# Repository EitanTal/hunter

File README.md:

# Intro

This is a recreation of an Old-school Hunter fan remote

## Digital signals

Every packet is as follows:

   [`address`][`opcode`]

address is 5 bits long, opcode is 8 bits long. Address used = 0b01111

### Packets & Opcodes

* light:    0x0F (01111) 0x1 (00000001)
* fan off:  0x0F (01111) 0x2 (00000010)
* fan rev:                   (00000100)
* fan 3:                     (00001000)
* fan 2:                     (00010000)
* fan 1:    0x0F             (00100000)

## Pulse layout

short pulse: (0)

      _
    __

long pulse: (1)

     __
    _

## Pulse timing

length of each character: 328.4us (0.3284ms)

every 1 bit = 8us.
41 bits = one unit.
~16 bytes per triplet.

This equals a baudrate of 3045

The bit burst must repeat 16 times.
There must be exactly 10ms gap between each bit burst.

## Radio notes

### Carrier

The chosen carrier is 302MHz. The original remote is inconsistent on its carrier wave, ranging from 300 to 305.

### Modulation

On-off-keying modulation is used. (AM)

### RF backend

This implementation utilizes TI CC1101 as the RF backend. The original hunter remote presumably used a ferrite core antenna. More details are available in eariler revisions.

As an antenna, a 30cm wire is used.

For power, 0db is currently used

## Breadboard notes

CC1101 operates on 3v3 max. Resistor divider used on Arduino -> CC1101

Relevant pins on the pinheader of the eval board of CC1101:
| Color   | Pin   |  |   Pin  | Color   |
|---------|-------|--|--------|---------|
|  Brown  | VCC   |  | VCC    | Red     |
|  Orange | SCK   |  | MOSI   | Yellow  |
|  Green  | GDO2  |  | MISO   | Blue    |
|  Purple | GDO0  |  | CSN    | Grey    |
|  White  | GND   |  | GND    | Black   |

The pins as they connect to my breadboard:
| Color   | Pin   |  |   Pin  | Color   |
|---------|-------|--|--------|---------|
| (Black) |GND    |  |    VCC |   (Red) |
| (Blue)  |MISO   |  |   MOSI |(Yellow) |
| (Orange)|SCK    |  |    CSN |  (Grey) |
|         |       |  |   GDO0 |(Purple) |

Relevant pins on the arduino:
|Number|Function|Comment                  |
|------|--------|-------------------------|
|10    | SS     | (Active low)            |
|11    | MOSI   |                         |
|12    | MISO   |                         |
|13    | SCLK   |                         |
|2     | GDO0   | (Interrupt line 0, PD2) |

Breadboard jumper cables:
arduino-breadboard line
2-21
7-19
10-15
11-13
12-17
13-9

## STM8 pins

|Arduino|Function|207K (Eval board)   |101F (Target)  |
|-------|--------|--------------------|---------------|
|10     | SS     |PE5 (D10)           |PB4            |
|11     | MOSI   |PC6 (D11)           |PB6            |
|12     | MISO   |PC7 (D12)           |PB7            |
|13     | SCLK   |PC5 (D13)           |PB5            |
|2      | GDO0   |PD0 (D2)            |PC0            |

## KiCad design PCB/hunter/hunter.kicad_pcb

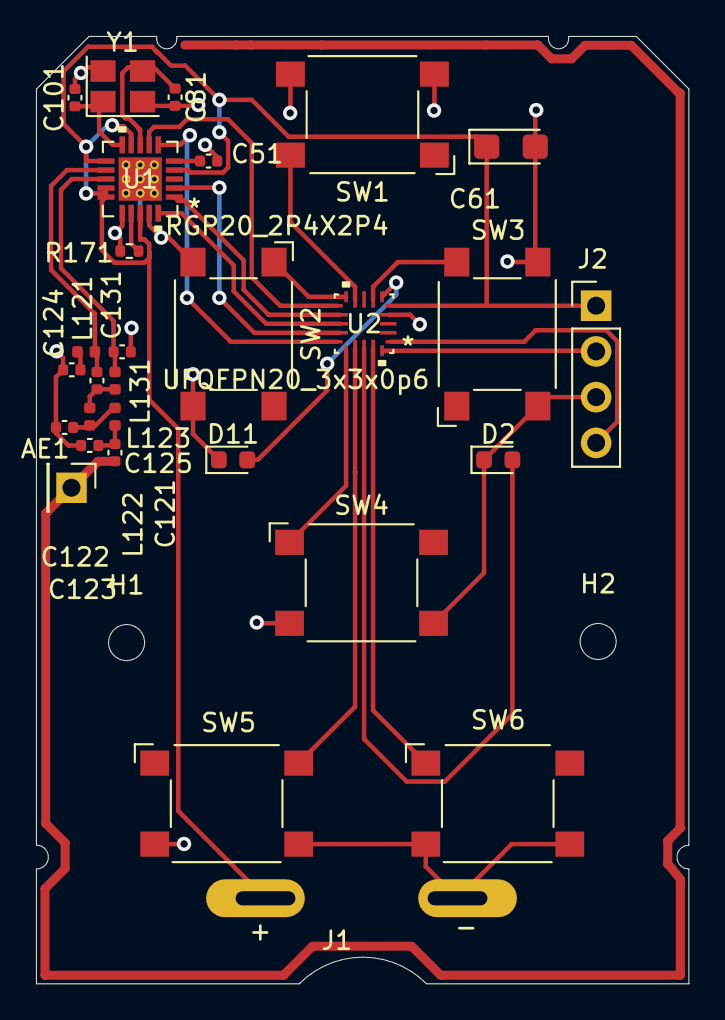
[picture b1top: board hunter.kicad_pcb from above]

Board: 2 copper layers, 36.2 x 52.6 mm, 31 parts (0 on the bottom side), 28 nets.

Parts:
AE1: Antenna; PinHeader_1x01_P2.54mm_Vertical
C51: 100nF; C_0402_1005Metric
C61: 10uF; CP_EIA-3216-18_Kemet-A
C81, C101: 27pF; C_0402_1005Metric
C121, C123, C131: 6.8pF; C_0402_1005Metric
C122: 12pF; C_0402_1005Metric
C124, C125: 220pF; C_0402_1005Metric
D2: LED2; LED_0603_1608Metric
D11: LED1; LED_0603_1608Metric
H1, H2: MountingHole; MountingHole_2mm
J1: Battery; MyBatteryConnector
J2: JTAG; PinHeader_1x04_P2.54mm_Vertical
L121, L123, L131: 33nH; L_0402_1005Metric
L122: 18nH; L_0402_1005Metric
R171: 56k; R_0402_1005Metric
SW1: SW_Light; SW_SPST_Omron_B3FS-100xP
SW2: SW_LightUp; SW_SPST_Omron_B3FS-100xP
SW3: SW_LightDown; SW_SPST_Omron_B3FS-100xP
SW4: SW_Fan; SW_SPST_Omron_B3FS-100xP
SW5: SW_FanUp; SW_SPST_Omron_B3FS-100xP
SW6: SW_FanDown; SW_SPST_Omron_B3FS-100xP
U1: RGP20_2P4X2P4; CC1101RGPR
U2: UFQFPN20_3x3x0p6; STM8L101F3U6TR
Y1: 25MHz; Crystal_SMD_3225-4Pin_3.2x2.5mm

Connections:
+3V0: C61.1, J1.1, J2.1, U1.4, U1.9, U1.11, U1.14, U1.15, U1.18, U2.5
GND: C51.2, C61.2, C81.1, C101.2, C122.2, C123.2, C124.2, C131.1, D2.1, D11.1, J1.2, J2.3, R171.1, SW1.3, SW1.4, SW2.3, SW2.4, SW3.3, SW3.4, SW4.3, SW4.4, SW5.3, SW5.4, SW6.3, SW6.4, U1.16, U1.19, U1.21, U1.V, U2.4, Y1.2, Y1.4
unnamed: AE1.1, C125.1
unnamed: C51.1, U1.5
unnamed: C81.2, U1.8, Y1.3
unnamed: C101.1, U1.10, Y1.1
unnamed: C121.1, L121.1, U1.12
unnamed: C121.2, L122.1, L131.2
unnamed: C122.1, L122.2, L123.1
unnamed: C123.1, C125.2, L123.2
unnamed: C124.1, L121.2
unnamed: C131.2, L131.1, U1.13
unnamed: D2.2, U2.18
unnamed: D11.2, U2.6
unnamed: J2.2, U2.20
unnamed: J2.4, U2.1
unnamed: R171.2, U1.17
unnamed: SW1.2, U2.9
unnamed: SW2.1, U2.10
unnamed: SW3.2, U2.7
unnamed: SW4.1, U2.16
unnamed: SW5.2, U2.17
unnamed: SW6.1, U2.19
unnamed: U1.1, U2.12
unnamed: U1.2, U2.14
unnamed: U1.6, U2.15
unnamed: U1.7, U2.11
unnamed: U1.20, U2.13

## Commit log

2021-08-07 Proven working version
2021-08-07 Notes of what I know so far...
2021-08-07 added circuit diagram + links
2021-08-20 waveform captures
2021-08-21 waveform characterisation
2021-08-22 ignore list, hunter LT spice circuit
2021-08-22 unsure about the phase angles. they're hard to measure.
2021-08-22 267MHz. pretty close.
2021-08-22 correct frequency reached
2021-08-22 more accurate inductor values?
2021-08-22 LED instead of diode
2021-08-24 attempt to install a switch
2021-09-22 import CC1101 lib
2021-09-22 button
2021-09-22 no longer use serial
2021-09-22 integration
2021-09-22 fix wrong memcpy size
2021-09-22 Integration with CC1101 OOK library (#1)
2021-09-24 Refactoring. (Squashed)
2021-09-24 ignorelist
2021-09-24 PCB outline
2021-09-24 formfactor pictures
2021-09-24 first button, correction to the board cut
2021-09-25 removal cont'd
2021-09-25 consolidation into init
2021-09-25 consolidation cont'd
2021-09-25 eliminate ctor
2021-09-25 cleanup cont'd
2021-09-25 cleanup
2021-09-25 class is now stateless
2021-09-25 class removal
2021-09-25 wipe the H file from unreferenced items
2021-09-25 eliminate spi class
2021-09-25 Refactoring: Simplify & Convert to C (#2)
2021-09-25 cubemx initial commit
2021-09-25 Pin rearrangement & renaming
2021-09-25 convert from arduino to stm8 - wip
2021-09-25 docs update (+1 squashed commits)
    Squashed commits:
    [1274bcd] docs
2021-09-25 project file initial commit
2021-09-25 ignorelist update
2021-09-25 rename cpp to c
2021-09-25 hunter.c build fix
2021-09-25 hunter_data build fix
2021-09-25 spi build fix
2021-09-25 code now builds. (with stubs)
2021-09-25 stmlib
2021-09-25 cont'd
2021-09-25 build config & fix
2021-09-26 Stm8 (#3)
2021-09-26 spi integration initial commit
2021-09-27 parts lib: cc1101, stm8l101, MyBatteryConnector
2021-09-28 button lib
2021-09-28 CPU: schematics
2021-09-28 CC1101 schematics, balun and anetanna
2021-09-28 Coupling capacitor, assign refences from datasheet
2021-09-28 CC1101: values and footprints
2021-09-28 rearrangement
2021-09-29 Schematics Complete, all foootprint assignments done
2021-09-29 PCB initial commit (#4)
    * PCB outline
    * first button, correction to the board cut
    * formfactor pictures
    * ignorelist
    * parts lib: cc1101, stm8l101, MyBatteryConnector
    * button lib
2021-09-29 pcb first attempt
    (cherry picked from commit e2accebbfe027ec41e787505fa792397e5ce38f1)
2021-09-29 main.c edits
2021-09-29 include hal library in project
2021-09-30 eval board docs
2021-09-30 use eval board mcu
2021-09-30 io.c initial implementation
2021-09-30 eval board cubemx initial commit
2021-10-01 STM8 pin mapping
2021-10-01 pullup
2021-10-02 gpio fixes
2021-10-03 readreg, test code
2021-10-03 refactoring
2021-10-03 some fixes
2021-10-03 signs of life from cc1101 & stm8. RF is produced
2021-10-04 hunter data rewrite
2021-10-04 time wip
2021-10-04 correct delay
2021-10-04 Full code port (into Nucleo) (#5)
2021-10-05 PCB wiring first attempt
2021-10-06 second attempt
2021-10-06 edits
2021-10-30 Move the CPU to the middle, longer antenna, button pinout fix, wider holes
2021-10-30 correct the crystal. LCSC part numbers
2021-10-30 no-op PCB change?
2021-10-30 scripty kicad script
2021-10-30 yet another no-op change
2021-10-30 correct LCSC parts for 0402 (and not 0603)
2021-10-30 minor changes, fixes to position output
2021-11-11 blinky and button on real hardware
2021-11-11 SPI pins
2021-11-11 misc fixes
2021-11-11 25mhz crystal compensation
2021-11-13 cleanups
2021-11-13 Migrate to real hardware (#6)
2021-11-13 rename the buttons
    (cherry picked from commit 16e04dbbbe135ee5b28e3ede6cda9ec160a9736c)
2021-11-13 refactoring initial commit
2021-11-13 error/limit animation
2021-11-13 power-save
2021-11-13 Full Functionality (#7)
2021-11-13 fixes
2021-11-13 bugfix
2021-11-13 Fully functional PCB (Phase 2) (#8)
2021-11-14 fan button toggles fan on and off. (instead of just off)
2024-07-23 current consumption fix attempt

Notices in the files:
parts and their libraries:
Copyright 2021 Accelerated Designs. All rights reserved.
